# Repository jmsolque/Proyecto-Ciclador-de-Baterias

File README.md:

# Proyecto-Ciclador-de-Baterias
Este repositorio contiene los archivos correspondientes a un ciclador de módulos de baterías.

## Documentación

### Componentes Utilizados
<div align="center">

| Componente | Cantidad | Modelo | Utilización |
|:----------:|:-----------:|:-----------:|:-----------:|
| Fuente de tensión | 1 | x | Alimentar algunos de los componentes utilizados. |
| Conversor DC/DC | 1 | TBA 1E | Tener tanto tensión positiva como negativa. |
| Varistor | 1 | x | Circuito de protección. |
| Resistencia 100 KΩ | 1 | x | Circuito de protección. |
| Diodo Zener | 1 | 1N4747 | Circuito de protección. |
| Transistor MOSFET | 1 | IRF9540N | Circuito de protección. |
| Transistor NPN | 2 | TIP120 | Uno para carga y otro para descarga. |
| Disipador Térmico | 2 | x | Disipar el calor de los transistores. |
| Inductor 10µH   | 2 | x | Dos, para regular corriente de carga y descarga y poder utilizar el sistema de control. |
| Amplificador Operacional | 1 | LM353 | Controlar si funciona el circuito de carga o de descarga. |
| Sensores de Corriente | 2 | x | Para medir las corrientes de carga y descarga. |
| Delfino | 1 | C2000 | Controlador. |
| Medidor de Tensión | 1 | x | Incorporado en el C2000, para medir la tensión de la batería. |
| Convertidor Digital Analógico | 1 | x | Controlar si descarga o carga. |

</div>

### Ecuaciones utilizadas

La ecuación utilizada para el circuito de carga es:

$$
0 = -V_{carga} + L\frac{di_c}{dt} + V_{batería} 
$$

De donde se tiene que:

$$
V_{carga} = V_{cc} + V_{cp} 
$$

Con base en lo anterior, se considera que: 

$$ 
V_{cp} = V_{\text{batería}} 
$$

Esta igualdad se logra mediante un sistema de prealimentación que compensa la caída de tensión en los elementos intermedios y asegura que el valor aplicado en el punto de control coincida con el voltaje real de la batería.

Por lo cual se tiene que:

$$
\frac{di_c}{dt} = \frac{V_{cc}}{L}
$$

Y de esta forma la función de transferencia será:

$$
\frac{i_c(s)}{V_{cc}(s)} = \frac{1}{Ls}
$$

De forma similar se tendrá para el el circuito de descarga, para el cual lo de realizar los cálculos pertinentes se tendría que la función de transferencia sería.

$$
\frac{i_c(s)}{V_{dc}(s)} = -\frac{1}{Ls}
$$

Donde Vdc es la tensión de descarga.

## [PLECS](PLECS/)

En esta sección se encuentra el código utilizado para la implementación en PLECS y así poder utilizar un C2000, en esta misma también se muestran las simualciones.

## [PCB](PCB/)

En esta sección se encuentran los archivos utilizados para la creación de la PCB.

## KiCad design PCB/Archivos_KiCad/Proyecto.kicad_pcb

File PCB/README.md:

# PCB

En esta sección se encuentran los archivos para la impresión de la PCB, junto con imágenes de referencia.

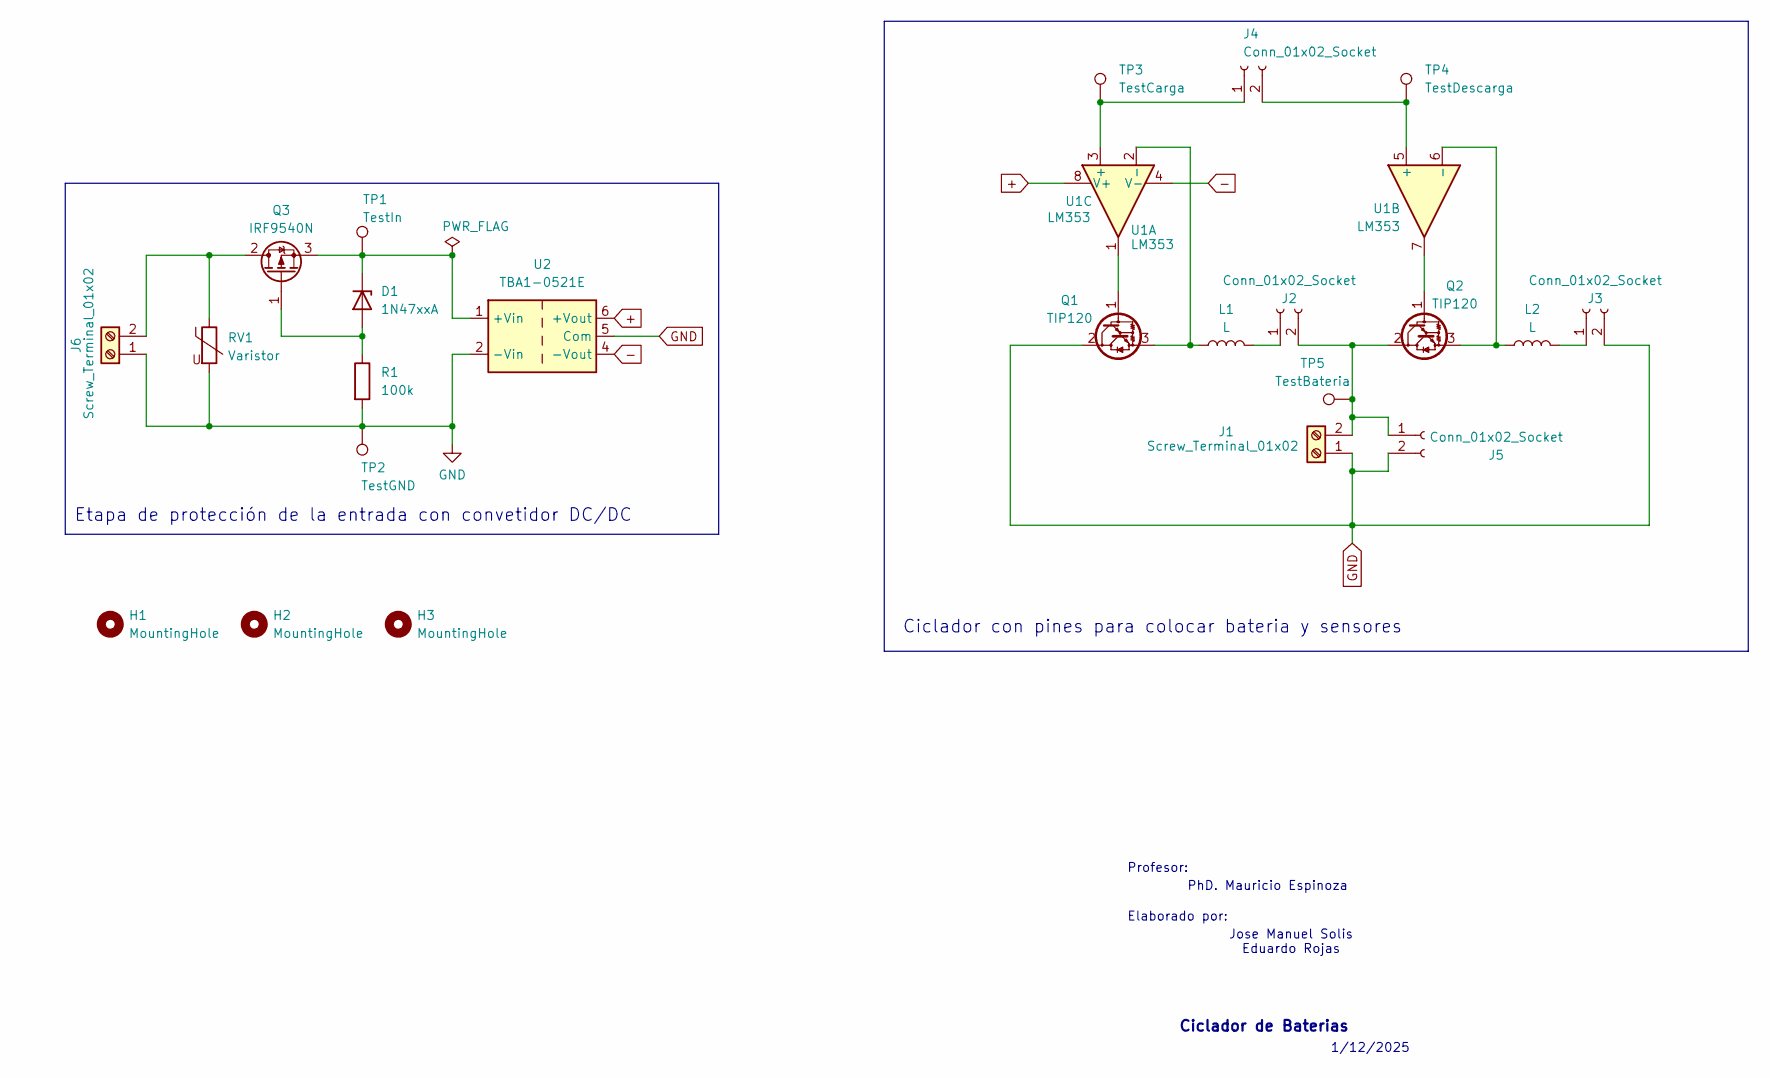
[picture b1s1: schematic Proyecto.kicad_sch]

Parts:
D1: 1N47xxA; D_DO-41_SOD81_P10.16mm_Horizontal
H1, H2, H3: MountingHole; MountingHole_2.2mm_M2
J1, J6: Screw_Terminal_01x02; TerminalBlock_Phoenix_MKDS-1,5-2_1x02_P5.00mm_Horizontal
J2, J3, J4, J5: Conn_01x02_Socket; PinSocket_1x02_P2.00mm_Vertical
L1, L2: L; L_Axial_L5.3mm_D2.2mm_P7.62mm_Horizontal_Vishay_IM-1
Q1, Q2: TIP120; TO-220-3_Vertical
Q3: IRF9540N; TO-220-3_Vertical
R1: 100k; R_Axial_DIN0207_L6.3mm_D2.5mm_P7.62mm_Horizontal
RV1: Varistor; RV_Disc_D7mm_W4mm_P5mm
TP1: TestIn; TestPoint_Loop_D2.54mm_Drill1.5mm_Beaded
TP2: TestGND; TestPoint_Loop_D2.54mm_Drill1.5mm_Beaded
TP3: TestCarga; TestPoint_Loop_D2.54mm_Drill1.5mm_Beaded
TP4: TestDescarga; TestPoint_Loop_D2.54mm_Drill1.5mm_Beaded
TP5: TestBateria; TestPoint_Loop_D2.54mm_Drill1.5mm_Beaded
U1: LM353; DIP-8_W7.62mm
U2: TBA1-0521E; Converter_DCDC_TRACO_TBA1-xxxxE_Dual_THT

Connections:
+: U1.8 (V+), U2.6 (+Vout)
-: U1.4 (V-), U2.4 (-Vout)
GND: J1.1, J3.2, J5.2, J6.1, Q1.2 (C), R1.2, RV1.2, TP2.1, U2.2 (-Vin), U2.5 (Com); also elsewhere on the board
unnamed: D1.2 (A), Q3.1 (G), R1.1
unnamed: D1.1 (K), Q3.3 (S), TP1.1, U2.1 (+Vin)
unnamed 5: J1.2, J2.2, J5.1, Q2.2 (C), TP5.1; also elsewhere on the board
unnamed: J2.1, L1.2
unnamed: J3.1, L2.2
unnamed: J4.1, TP3.1, U1.3 (+)
unnamed: J4.2, TP4.1, U1.5 (+)
unnamed 10: J6.2, Q3.2 (D), RV1.1; also elsewhere on the board
unnamed: Q1.1 (B), U1.1
unnamed: L1.1, Q1.3 (E), U1.2 (-)
unnamed: Q2.1 (B), U1.7
unnamed: L2.1, Q2.3 (E), U1.6 (-)

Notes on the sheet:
Jose Manuel Solis Eduardo Rojas
1/12/2025
Elaborado por:
Profesor:
Ciclador con pines para colocar bateria y sensores
Ciclador de Baterias
Etapa de protección de la entrada con convetidor DC/DC
PhD. Mauricio Espinoza

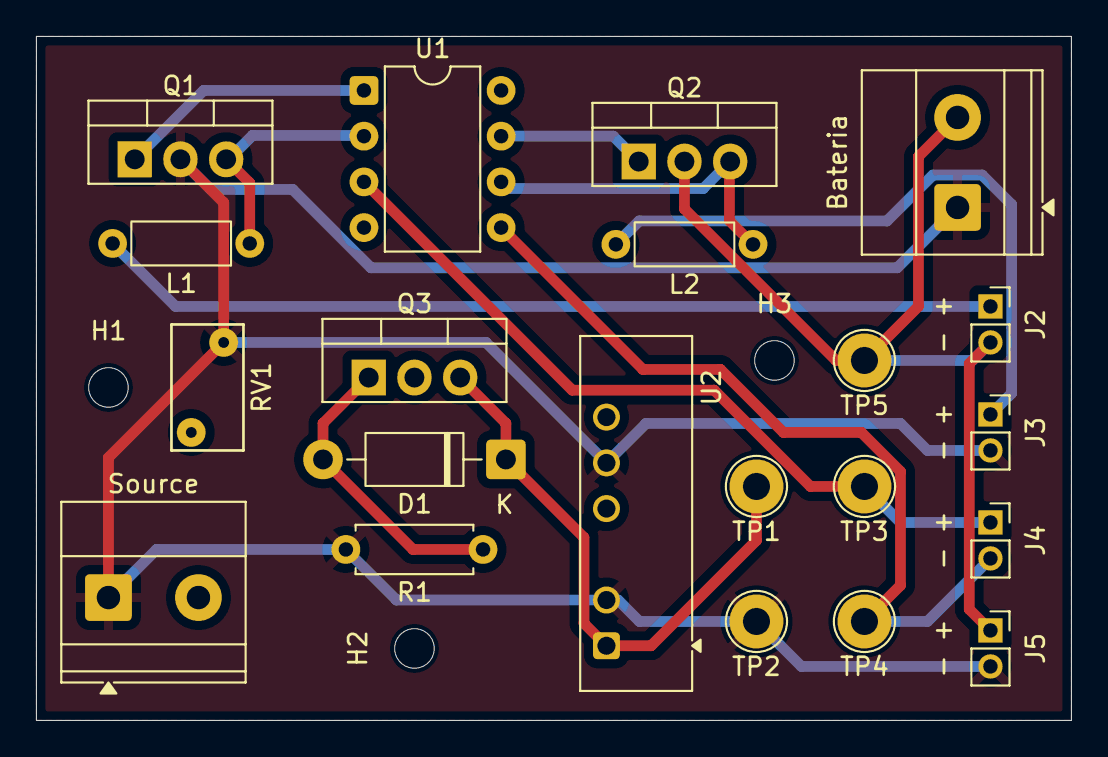
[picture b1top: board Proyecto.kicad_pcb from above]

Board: 4 copper layers, 57.5 x 38.0 mm, 24 parts (0 on the bottom side), 15 nets.

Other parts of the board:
Bateria: Screw_Terminal_01x02; TerminalBlock_Phoenix_MKDS-1,5-2_1x02_P5.00mm_Horizontal
Source: Screw_Terminal_01x02; TerminalBlock_Phoenix_MKDS-1,5-2_1x02_P5.00mm_Horizontal

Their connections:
GND: Bateria.1, Source.1; also elsewhere on the board
unnamed 5: Bateria.2; also elsewhere on the board
unnamed 10: Source.2; also elsewhere on the board

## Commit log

2025-12-02 Se agrega el .plecs
2025-12-02 Arreglo
2025-12-02 Cambios
2025-12-03 Prueba
2025-12-03 Ajustes
2025-12-03 Ajustes y se agregan ecuaciones
2025-12-03 Arreglos
2025-12-03 Mejoras
2025-12-03 Se agregan carpetas y archivos
2025-12-03 Ajuste
